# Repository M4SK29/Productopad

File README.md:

# Productopad
My macropad for productivity, allowing to open and close apps at the click of buttons!

## Notes
1. I'll not be attaching the 4 pin headers themselves to the pcb but will use their holes and solder my cables to them to make it easier.
2. The platform sorta thing you see on the design is the place for the 0.91 inch oled. tightly fitted, yes and I won't be putting headers on that either I'll just solder the cables to the holes.
3. To fix the screen to the platform I'll probably just hotglue it. It's convenient and can be removed when needed then.
4. Yes the code is written by ChatGPT, so I'll probably have to edit it and make it work when I receive the parts.

## Hackpad

## Schematic

## PCB

## Case and it's parts

This is the base of it and

this is the top

I will connect the cables for the OLED screen and glue it to the sort of platform I've made. It will be a tight fit so I may even not need to use the glue. The top will then be put on with nut and bolts or whatever they provide in the kit for it. That's pretty much it for putting the things in the case and like I said I'll be soldering the cables for the display and not use the headers(4 pin ones)

## Fitting
PCB in base:

top on base:

### Fitting the OLED Display:
The OLED display will be put right here(in the following image) where I've cut a place for it to be there(exact dimensions)

After that I also have made some space for the jumper cables that I'll be soldering to it, here-

## List of parts needed-
(the number in brackets is the needed quantity)
1. Seeed XIAO RP2040(1)
2. Blank DSA keycaps(4)
3. SK6812 MINI-E LED(1)
4. 0.91 inch OLED display(1)
5. MX-Style switches(4)
6. M3x16mm screws(6)
7. 3D Printed case(I don't have a 3D printer)
8. Jumper cables(4 male to male)(or I'll get that by myself from somewhere cuz it wasnt there in the list of approved parts)

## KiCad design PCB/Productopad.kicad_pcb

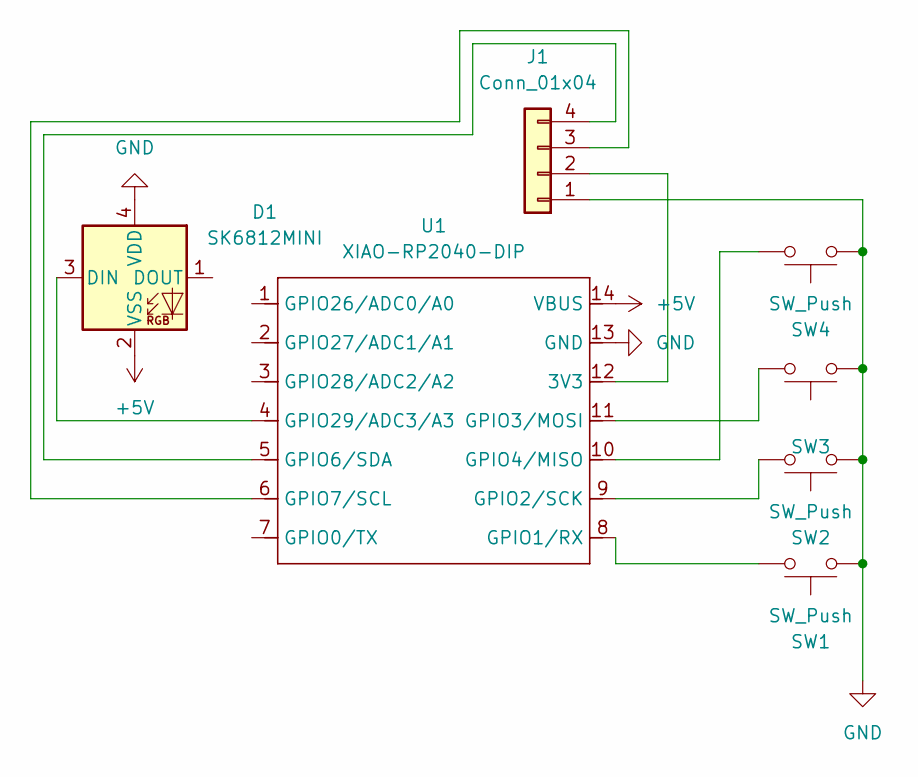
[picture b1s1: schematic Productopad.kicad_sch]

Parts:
D1: SK6812MINI; LED_SK6812MINI_PLCC4_3.5x3.5mm_P1.75mm
J1: Conn_01x04; PinHeader_1x04_P2.54mm_Vertical
SW1, SW2, SW3, SW4: SW_Push; SW_Cherry_MX_1.00u_PCB
U1: XIAO-RP2040-DIP

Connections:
+5V: D1.2 (VSS), U1.14 (VBUS)
GND: D1.4 (VDD), J1.1, SW1.1, SW2.1, SW3.1, SW4.1, U1.13 (GND)
unnamed: D1.3 (DIN), U1.4 (GPIO29/ADC3/A3)
unnamed: J1.2, U1.12 (3V3)
unnamed: J1.3, U1.6 (GPIO7/SCL)
unnamed: J1.4, U1.5 (GPIO6/SDA)
unnamed: SW1.2, U1.8 (GPIO1/RX)
unnamed: SW2.2, U1.9 (GPIO2/SCK)
unnamed: SW3.2, U1.11 (GPIO3/MOSI)
unnamed: SW4.2, U1.10 (GPIO4/MISO)

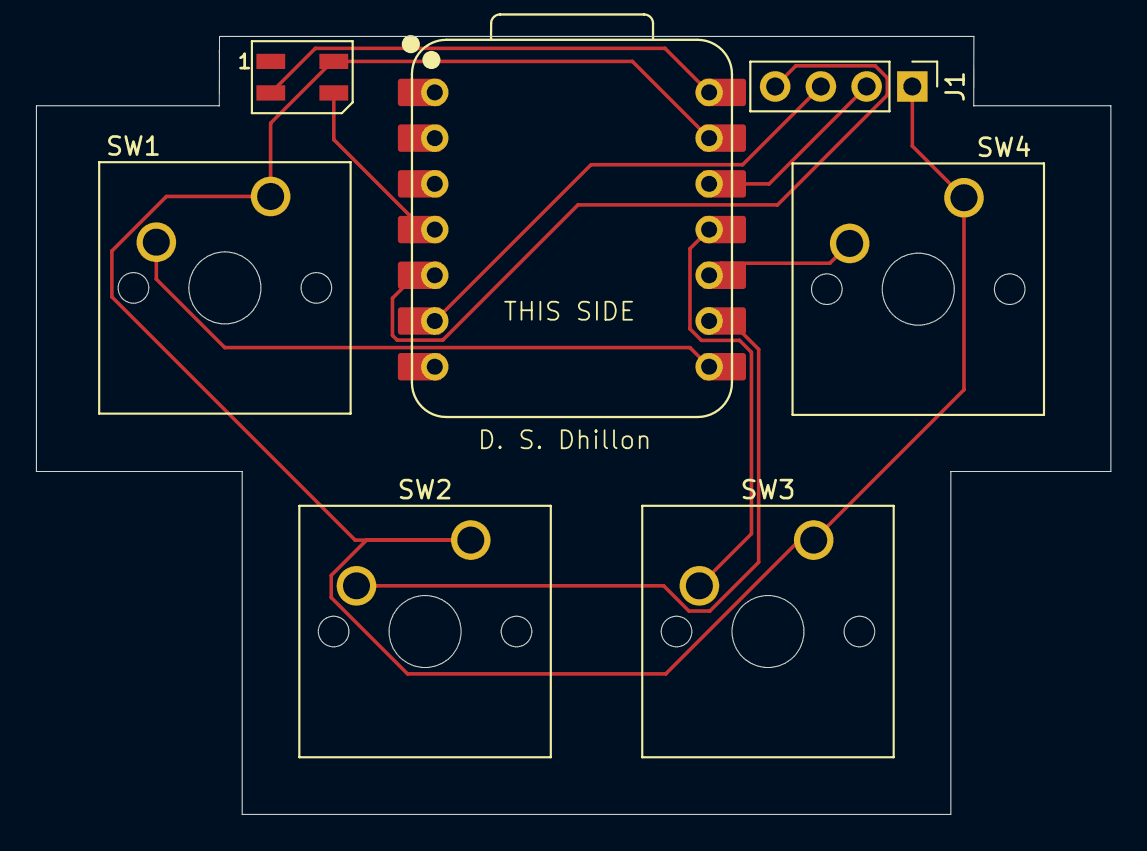
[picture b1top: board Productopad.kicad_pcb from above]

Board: 2 copper layers, 59.7 x 43.2 mm, 7 parts (0 on the bottom side), 10 nets.

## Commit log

2025-12-18 Add README
2025-12-25 Fixed position for OLED
